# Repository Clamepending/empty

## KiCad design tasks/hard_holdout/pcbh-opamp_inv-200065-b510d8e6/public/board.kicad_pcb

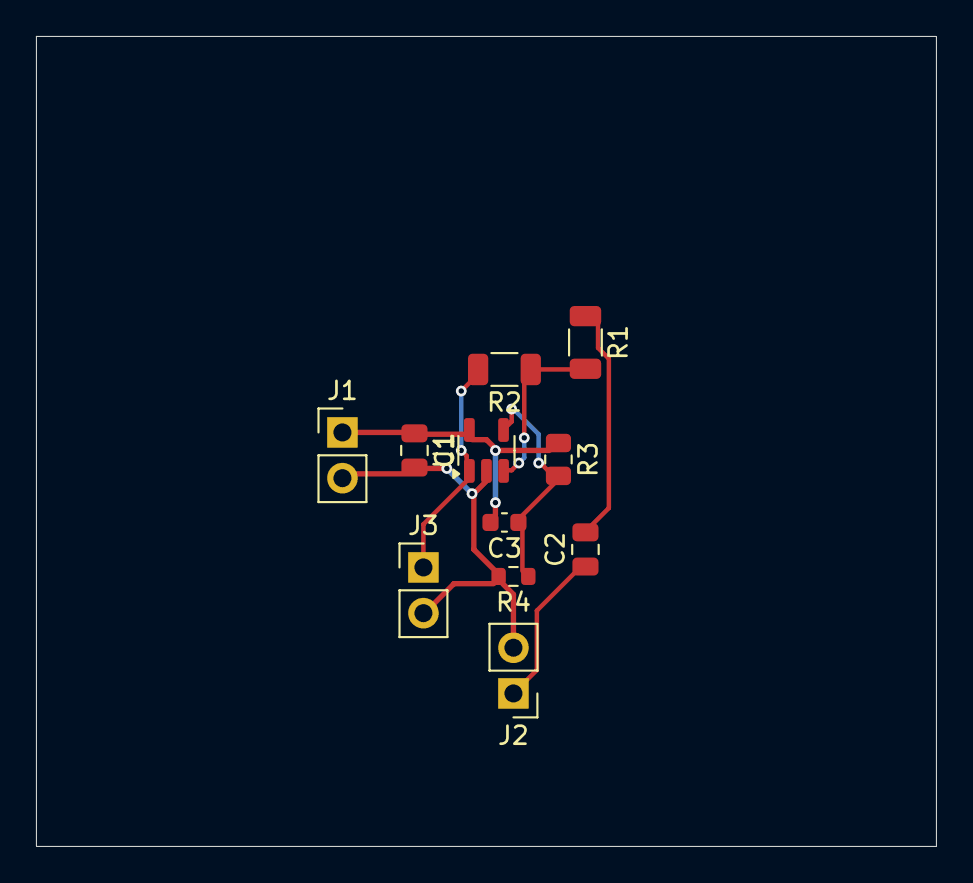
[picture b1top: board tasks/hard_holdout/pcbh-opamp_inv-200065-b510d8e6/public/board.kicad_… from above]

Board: 2 copper layers, 50.0 x 45.0 mm, 11 parts (0 on the bottom side), 7 nets.

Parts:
C1: 100n; C_0805_2012Metric
C2: 220n; C_0805_2012Metric
C3: 4.7u; C_0603_1608Metric
J1, J2, J3: PinHeader_1x02_P2.54mm_Vertical
R1: 6.19k; R_1206_3216Metric
R2: 61.9k; R_1206_3216Metric
R3: 5.6k; R_0805_2012Metric
R4: 27k; R_0603_1608Metric
U1: SOT-23-5

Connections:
GND: C1.2, J1.2, J2.2, J3.2, R4.2, U1.2
IN: C2.1, J2.1
IN_AC: C2.2, R1.1
OUT: J3.1, R2.2, U1.1
SUM: R1.2, R2.1, U1.3
VCC: C1.1, C3.2, J1.1, R3.1, U1.5
VMID: C3.1, R3.2, R4.1, U1.4

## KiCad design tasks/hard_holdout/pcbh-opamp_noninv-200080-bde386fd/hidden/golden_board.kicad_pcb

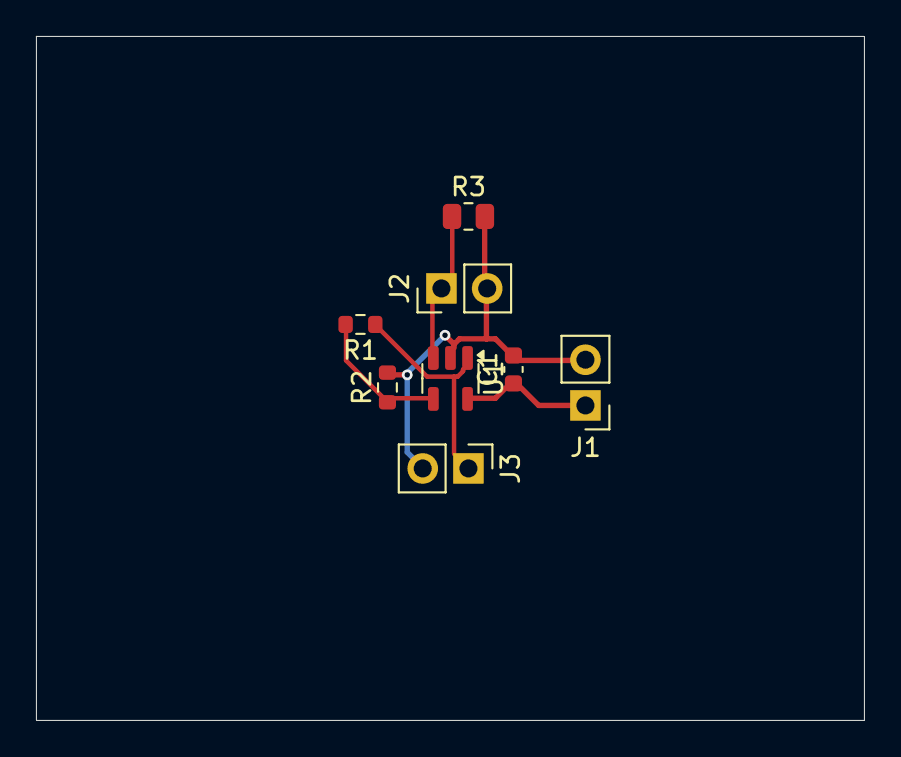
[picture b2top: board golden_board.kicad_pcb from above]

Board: 2 copper layers, 46.0 x 38.0 mm, 8 parts (0 on the bottom side), 5 nets.

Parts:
C1: 100n; C_0603_1608Metric
J1, J2, J3: PinHeader_1x02_P2.54mm_Vertical
R1: 53.6k; R_0603_1608Metric
R2: 7.68k; R_0603_1608Metric
R3: 220k; R_0805_2012Metric
U1: SOT-23-5

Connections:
FB: R1.2, R2.1, U1.4
GND: C1.2, J1.2, J2.2, J3.2, R2.2, R3.2, U1.2
IN: J2.1, R3.1, U1.3
OUT: J3.1, R1.1, U1.1
VCC: C1.1, J1.1, U1.5

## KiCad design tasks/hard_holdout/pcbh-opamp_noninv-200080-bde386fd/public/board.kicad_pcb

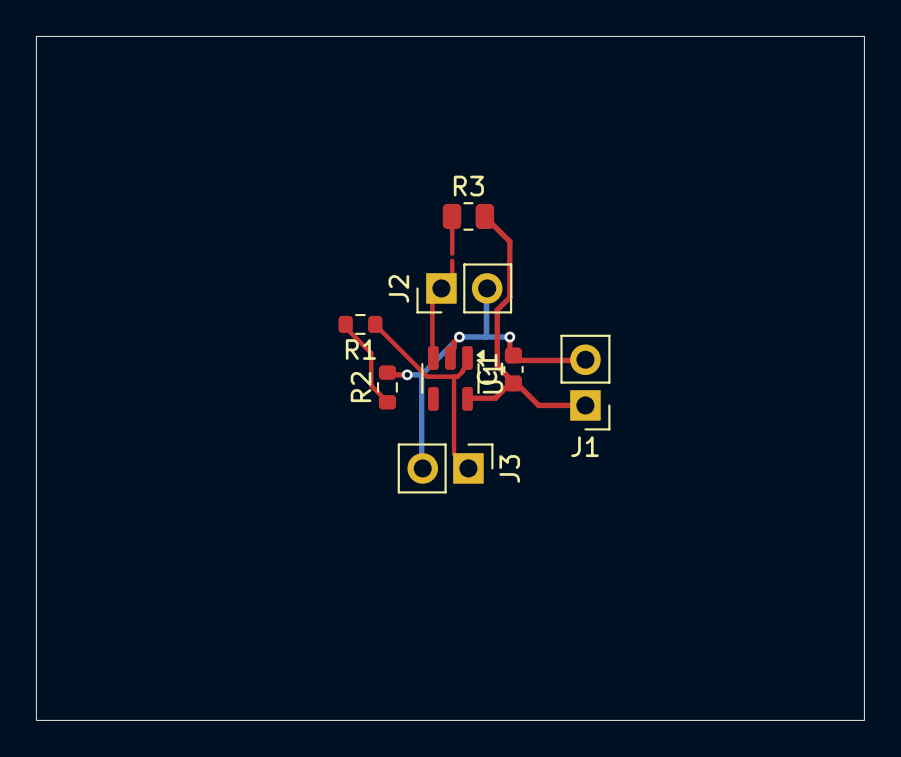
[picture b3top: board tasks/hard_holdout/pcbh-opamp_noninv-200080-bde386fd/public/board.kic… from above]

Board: 2 copper layers, 46.0 x 38.0 mm, 8 parts (0 on the bottom side), 5 nets.

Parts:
C1: 100n; C_0603_1608Metric
J1, J2, J3: PinHeader_1x02_P2.54mm_Vertical
R1: 53.6k; R_0603_1608Metric
R2: 7.68k; R_0603_1608Metric
R3: 220k; R_0805_2012Metric
U1: SOT-23-5

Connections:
FB: R1.2, R2.1
GND: C1.2, J1.2, J2.2, J3.2, R2.2, U1.2
IN: J2.1, R3.1, U1.3
OUT: J3.1, R1.1, U1.1
VCC: C1.1, J1.1, R3.2, U1.5
